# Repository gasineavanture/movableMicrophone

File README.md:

## Remote-Controlled Height-Adjustable Microphone Stand

### Project Overview
 
This project focuses on redesigning and improving an existing prototype of a microphone stand with remotely adjustable height. The stand allows users to change the microphone height to suit different speakers using a mobile application over Wi-Fi.

The existing design uses an electric motor and a lead-screw mechanism for controlled vertical positioning. The goal is to improve the mechanical design, electronics, software, and battery-powered operation.

### Project Goals

• Redesign selected mechanical parts and create 3D-printable components.

• Update the electrical schematic and design a printed circuit board (PCB).

• Improve motor position control and Wi-Fi communication.

• Optimize the battery power system.

• Assemble and test the improved prototype.

• Evaluate the product’s potential applications and market viability.

### Components and References

• Microcontroller: Seeed Studio XIAO ESP32S3 — Wi-Fi-enabled development board.

• DC motor reference: Escap / Portescap motor documentation — see ESCAP.pdf and Escap_datasheet.pdf (exact motor variant not specified).

• Additional component catalogue: Hypex catalogue.

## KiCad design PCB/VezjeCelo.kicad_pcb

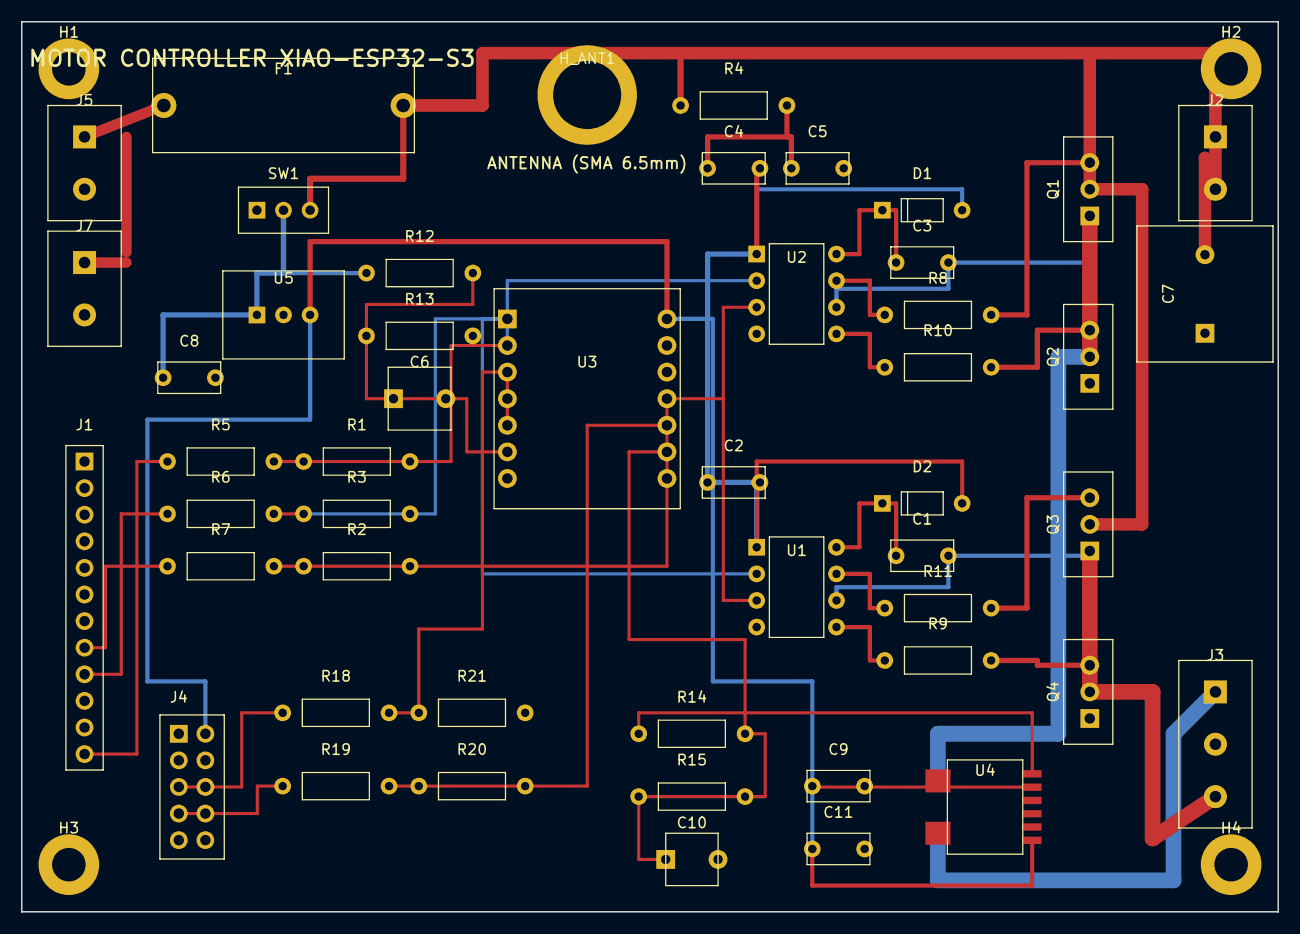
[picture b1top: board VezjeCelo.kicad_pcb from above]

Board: 2 copper layers, 120.0 x 85.0 mm, 54 parts (0 on the bottom side), 33 nets.

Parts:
C1, C2, C3, C4, C5: 0.1uF; C_Disc_D5.0mm_W2.5mm_P5.00mm
C6: 10uF; CP_Radial_D6.0mm_P5.00mm
C7: 2200uF/25V; CP_Radial_D13.0mm_P7.50mm
C8: C; C_Disc_D5.0mm_W2.5mm_P5.00mm
C9, C11: 47nF; C_Disc_D5.0mm_W2.5mm_P5.00mm
C10: 1uF; CP_Radial_D5.0mm_P5.00mm
D1, D2: D; D_DO-35_SOD27_P7.62mm_Horizontal
F1: Fuse; Fuseholder_Cylinder-5x20mm_Horizontal
H1, H2, H3, H4: MountingHole_3.2mm_M3; MountingHole_3.2mm_M6_SMA_Antenna_Pad
H_ANT1: SMA_Antenna_Hole_6.5mm; MountingHole_6.5mm_M6_SMA_Antenna_Pad
J1: J1; PinHeader_1x12_P2.54mm_Vertical
J2: J2; TerminalBlock_Phoenix_MKDS-1,5-2_1x02_P5.00mm_Horizontal
J3: Motor; TerminalBlock_Phoenix_MKDS-1,5-3_1x03_P5.00mm_Horizontal
J4: Enkoder; PinHeader_2x05_P2.54mm_Vertical
J5: Polnilec; TerminalBlock_Phoenix_MKDS-1,5-2_1x02_P5.00mm_Horizontal
J7: Baterija; TerminalBlock_Phoenix_MKDS-1,5-2_1x02_P5.00mm_Horizontal
Q1, Q2, Q3, Q4: IRF540Z; TO-220-3_Vertical
R1, R2, R3: 10 K; R_Axial_DIN0207_L6.3mm_D2.5mm_P10.16mm_Horizontal
R4, R8, R9, R10, R11: 22 R; R_Axial_DIN0207_L6.3mm_D2.5mm_P10.16mm_Horizontal
R5, R6, R7: 1 K; R_Axial_DIN0207_L6.3mm_D2.5mm_P10.16mm_Horizontal
R12: 33 K; R_Axial_DIN0207_L6.3mm_D2.5mm_P10.16mm_Horizontal
R13: 6K8; R_Axial_DIN0207_L6.3mm_D2.5mm_P10.16mm_Horizontal
R14: 10K; R_Axial_DIN0207_L6.3mm_D2.5mm_P10.16mm_Horizontal
R15: 15K; R_Axial_DIN0207_L6.3mm_D2.5mm_P10.16mm_Horizontal
R18, R19: 2K2; R_Axial_DIN0207_L6.3mm_D2.5mm_P10.16mm_Horizontal
R20, R21: 3K3; R_Axial_DIN0207_L6.3mm_D2.5mm_P10.16mm_Horizontal
SW1: SW_SPDT; SW_Slide_1P2T_CK_OS102011MS2QN1
U1, U2: IR2104; DIP-8_W7.62mm
U3: XIAO-ESP32-S3; Seeed_Studio_XIAO_Series_DIP
U4: LEM HMSR 6-SMS; LEM_HMSR_6-SMS
U5: R-785.0-0.5; Converter_DCDC_RECOM_R-78E-0.5_THT

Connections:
+5V: C11.1, J4.2, U3.14, U4.10, U5.3
+12V: C7.1, F1.2, J2.2, Q1.2, Q3.2, R4.1, SW1.3
DRIVER_SD_N: R2.1, R7.2, U1.3, U2.3, U3.11
ENC_A: R18.2, R21.1, U3.3, U3.5
ENC_A_RAW: J4.5, R18.1
ENC_B: R19.2, R20.1, U3.10
ENC_B_RAW: J4.7, R19.1
GND: C2.2, C4.2, C5.2, C6.2, C7.2, C8.2, C9.2, C10.2, C11.2, H1.1, H2.1, H3.1, H4.1, H_ANT1.1, J1.1, J2.1, J3.2, J4.3, J5.2, J7.2, Q2.3, Q4.3, R1.2, R2.2, R3.2, R13.2, R15.2, R20.2, R21.2, U1.4, U2.4, U3.13, U4.9, U5.2
ISENSE_OUT: C10.1, R14.2, R15.1, U3.9
ISENSE_RAW: R14.1, U4.5
J1_8: J1.8, R7.1
J1_9: J1.9, R6.1
J1_12: J1.12, R5.1
MOTOR_A: J3.1, U4.3
PHASE_A: C3.2, Q1.3, Q2.2, U2.6, U4.1
PHASE_B: C1.2, J3.3, Q3.3, Q4.2, U1.6
PWM_A: R1.1, R5.2, U2.2, U3.2
PWM_B: R3.1, R6.2, U1.2, U3.1
Q1_G: Q1.1, R8.2
Q2_G: Q2.1, R10.2
Q3_G: Q3.1, R11.2
Q4_G: Q4.1, R9.2
U1_HO_GATE: R11.1, U1.7
U1_LO_GATE: R9.1, U1.5
U1_VB: C1.1, D2.1, U1.8
U2_HO_GATE: R8.1, U2.7
U2_LO_GATE: R10.1, U2.5
U2_VB: C3.1, D1.1, U2.8
U4_VREF: C9.1, U4.6
VBAT_IN: F1.1, J5.1, J7.1
VBAT_SW: C8.1, R12.1, SW1.2, U5.1
VDRV_12V: C2.1, C4.1, C5.1, D1.2, D2.2, R4.2, U1.1, U2.1
VSENSE_BAT: C6.1, R12.2, R13.1, U3.6
